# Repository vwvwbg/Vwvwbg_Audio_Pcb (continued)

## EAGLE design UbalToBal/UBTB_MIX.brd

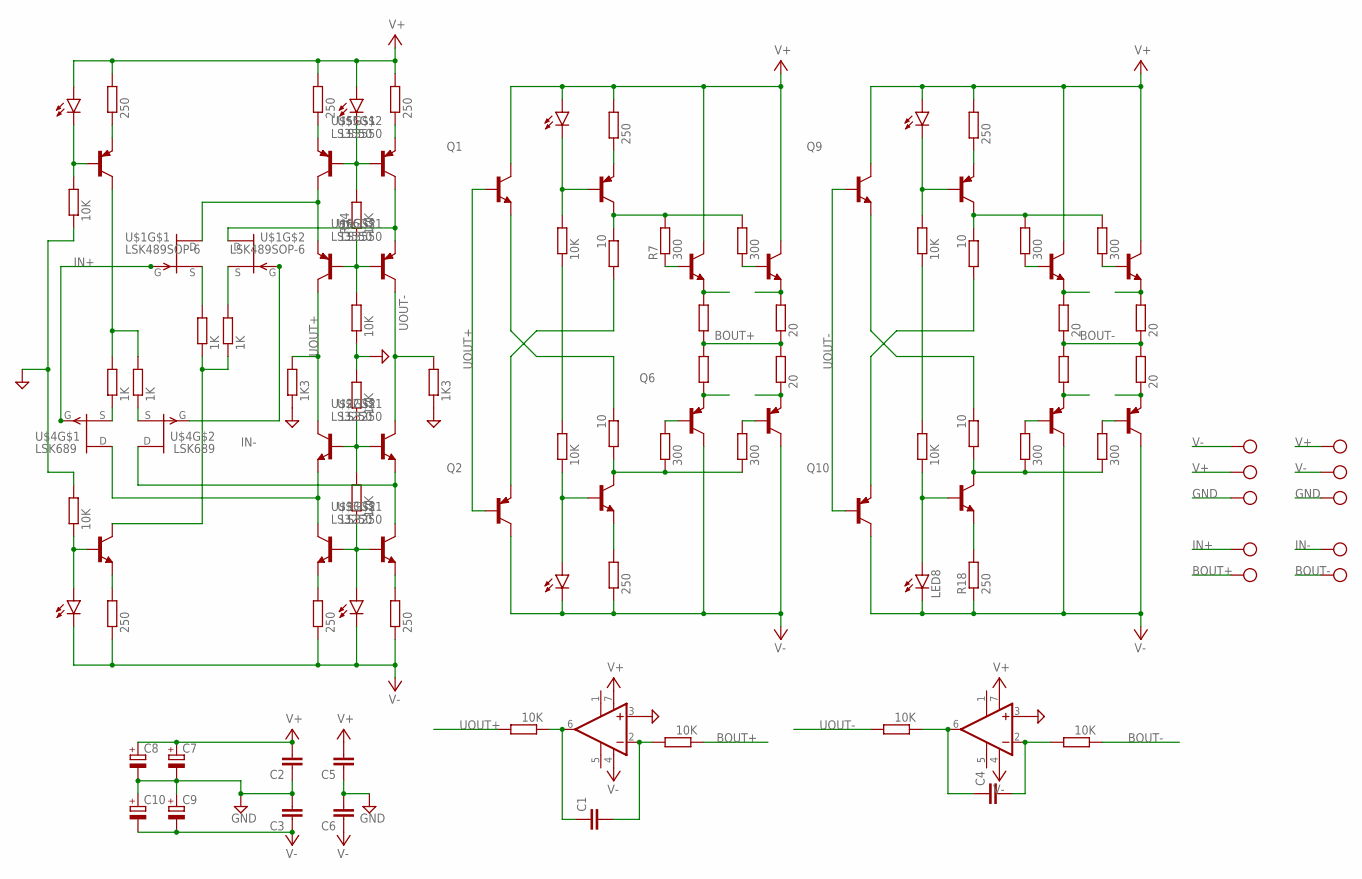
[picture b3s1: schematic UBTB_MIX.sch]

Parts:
C1, C4: C-EUC1206; C1206
C2, C3, C5, C6: C-EUC0805; C0805
C7, C8, C9, C10: CPOL-EUF; PANASONIC_F
IC1, IC2: OPA627U; SO08
LED1, LED2, LED3, LED4, LED5, LED6, LED7, LED8: LEDVWV1206; LED_SML1206
Q1, Q3, Q5, Q8, Q9, Q11, Q13, Q14, Q17: TRANSISTOR_BC846-NPN-SOT23-BEC; TRANSISTOR_SOT23-BEC
Q2, Q4, Q6, Q7, Q10, Q12, Q15, Q16, Q18: TRANSISTOR_BC856B-PNP-SOT23-BEC; TRANSISTOR_SOT23-BEC
R1, R2, R15, R18, R22, R23, R35, R36, R43, R44: 250; MINI_MELF-0204W
R3, R4, R16, R17, R19, R20, R29, R32, R33, R34, R45, R46, R48, R51: 10K; MINI_MELF-0204W
R5, R6, R21, R24: 10; MINI_MELF-0204W
R7, R8, R9, R10, R25, R26, R27, R28: 300; MINI_MELF-0204W
R11, R12, R31: R-EU_MELF0204W; MINI_MELF-0204W
R13, R14, R30, R47, R49: 20; MINI_MELF-0204W
R37, R38: 1K3; MINI_MELF-0204W
R39, R40, R41, R42: 1K; MINI_MELF-0204W
U$1: LSK489SOP-6; SOT-23-6
U$2, U$3: LS3250; SOT-23-6
U$4: LSK689; SOT-23-6
U$5, U$6: LS3550; SOT-23-6
X1, X2: CON-PHOENIX-508_MKDSN1,5/3-5,08
X3, X4: CON-PHOENIX-508_MKDSN1,5/2-5,08

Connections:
BOUT+: R11.1, R12.2, R13.1, R14.2, R17.1, X3.2
BOUT-: R30.1, R31.2, R47.1, R48.1, R49.2, X4.2
GND: C2.1, C3.2, C5.1, C6.2, C7.-, C8.-, C9.+, C10.+, IC1.3 (+IN), IC2.3 (+IN), R32.2, R33.1, R37.1, R38.1, R45.1, R46.2, X1.3, X2.3
IN+: U$1.1 (G), U$4.1 (G), X3.1
IN-: U$1.4 (G), U$4.4 (G), X4.1
unnamed: C4.1, IC2.6 (OUT), R51.1
unnamed: R35.1, U$5.2 (E)
unnamed: C4.2, IC2.2 (-IN), R48.2
unnamed: Q2.E, R5.2
unnamed: Q3.E, R2.2
unnamed: Q4.E, R1.1
unnamed: LED5.C, Q4.B, R3.2
unnamed: LED6.A, Q3.B, R4.1
unnamed: Q4.C, R5.1, R7.2, R10.2
unnamed: Q3.C, R6.2, R8.1, R9.1
unnamed: Q1.E, R6.1
unnamed: R3.1, R4.2
unnamed: Q5.B, R7.1
unnamed: Q5.E, R11.2
unnamed: Q7.B, R9.2
unnamed: Q8.B, R10.1
unnamed: Q6.B, R8.2
unnamed: Q6.E, R12.1
unnamed: C1.2, IC1.2 (-IN), R17.2
unnamed: Q8.E, R13.2
unnamed: Q7.E, R14.1
unnamed: C1.1, IC1.6 (OUT), R16.1
unnamed: R36.1, U$5.5 (E)
unnamed: Q11.E, R18.2
unnamed: Q12.E, R15.1
unnamed: LED7.C, Q12.B, R19.2
unnamed: LED8.A, Q11.B, R20.1
unnamed: Q12.C, R21.1, R25.2, R28.2
unnamed: Q11.C, R24.2, R26.1, R27.1
unnamed: Q10.E, R21.2
unnamed: Q9.E, R24.1
unnamed: R19.1, R20.2
unnamed: Q13.B, R25.1
unnamed: Q15.B, R26.2
unnamed: Q14.B, R28.1
unnamed: Q16.B, R27.2
unnamed: Q13.E, R30.2
unnamed: Q15.E, R31.1
unnamed: Q14.E, R47.2
unnamed: Q16.E, R49.1
unnamed: R22.2, U$3.5 (E)
unnamed: R23.2, U$3.2 (E)
unnamed: U$2.2 (E), U$3.4 (C), U$4.5 (D)
unnamed: U$2.5 (E), U$3.6 (C), U$4.2 (D)
unnamed: LED1.A, R29.1, U$3.1 (B), U$3.3 (B)
unnamed: R29.2, R32.1, U$2.1 (B), U$2.3 (B)
unnamed: R33.2, R34.1, U$6.1 (B), U$6.3 (B)
unnamed: U$1.2 (D), U$5.4 (C), U$6.5 (E)
unnamed: LED2.C, R34.2, U$5.1 (B), U$5.3 (B)
unnamed: U$1.5 (D), U$5.6 (C), U$6.2 (E)
unnamed: LED3.C, Q18.B, R45.2
unnamed: Q18.E, R43.1
unnamed: Q18.C, R41.2, R42.2
unnamed: R42.1, U$4.6 (S)
unnamed: R41.1, U$4.3 (S)
unnamed: R39.2, U$1.3 (S)
unnamed: R40.2, U$1.6 (S)
unnamed: Q17.C, R39.1, R40.1
unnamed: Q17.E, R44.2
unnamed: LED4.A, Q17.B, R46.1
UOUT+: Q1.B, Q2.B, R16.2, R37.2, U$2.6 (C), U$6.6 (C)
UOUT-: Q9.B, Q10.B, R38.2, R51.2, U$2.4 (C), U$6.4 (C)
V+: C2.2, C5.2, C7.+, C8.+, IC1.7 (V+), IC2.7 (V+), LED2.A, LED3.A, LED5.A, LED7.A, Q1.C, Q5.C, Q8.C, Q9.C, Q13.C, Q14.C, R1.2, R15.2, R35.2, R36.2, R43.2, X1.2, X2.1
V-: C3.1, C6.1, C9.-, C10.-, IC1.4 (V-), IC2.4 (V-), LED1.C, LED4.C, LED6.C, LED8.C, Q2.C, Q6.C, Q7.C, Q10.C, Q15.C, Q16.C, R2.1, R18.1, R22.1, R23.1, R44.1, X1.1, X2.2

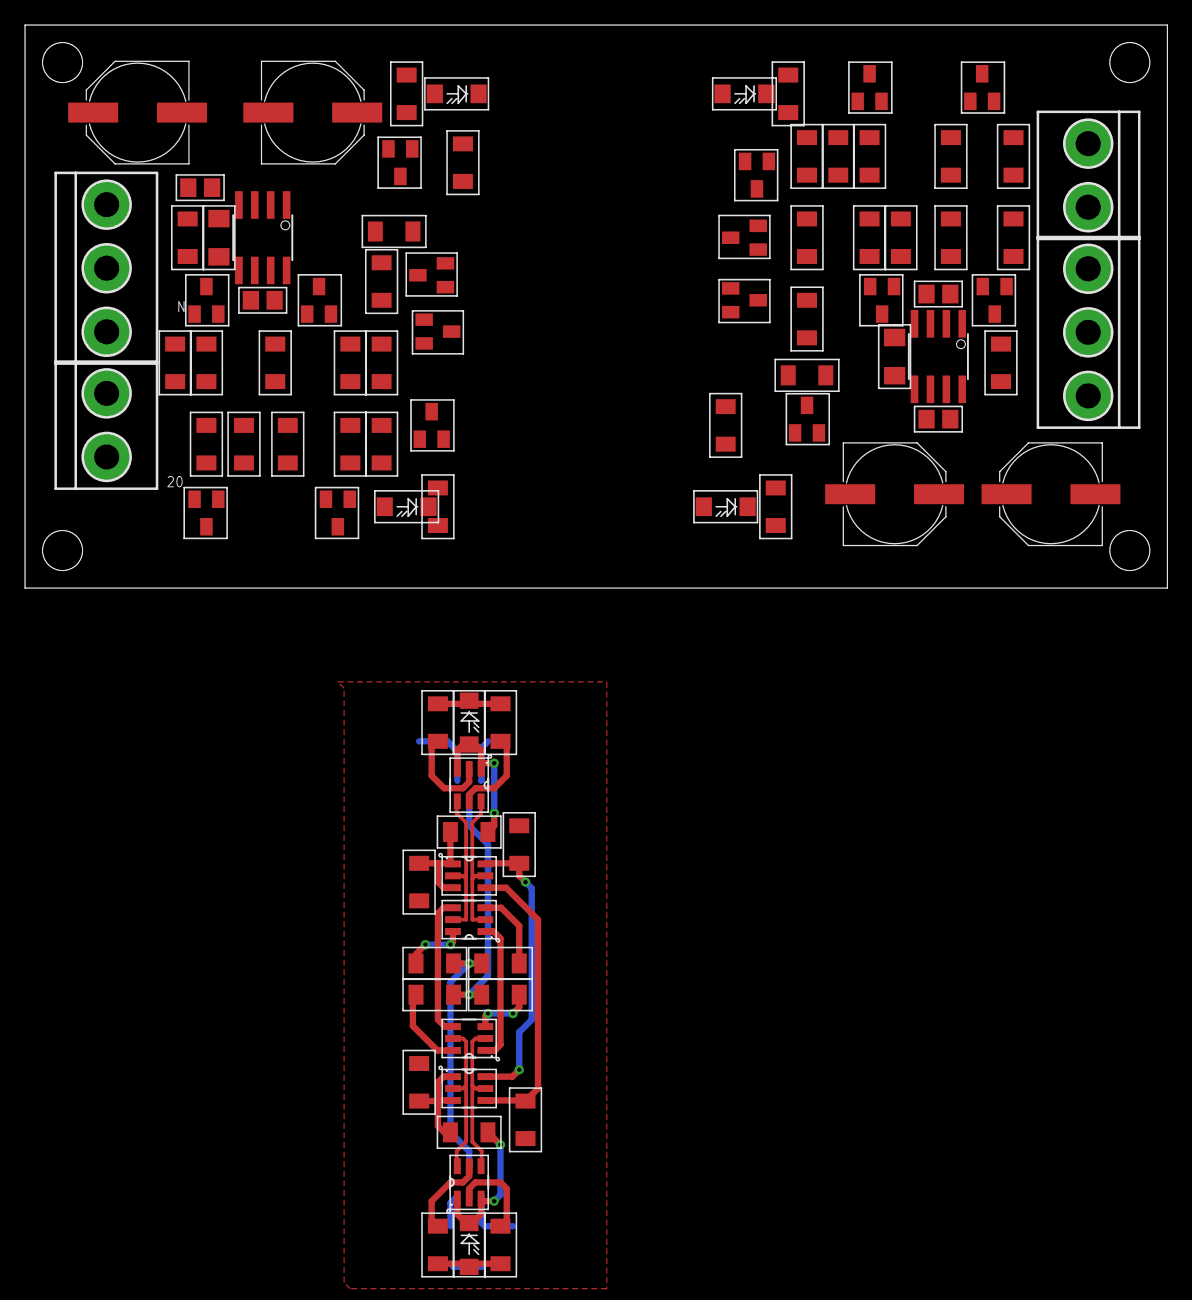
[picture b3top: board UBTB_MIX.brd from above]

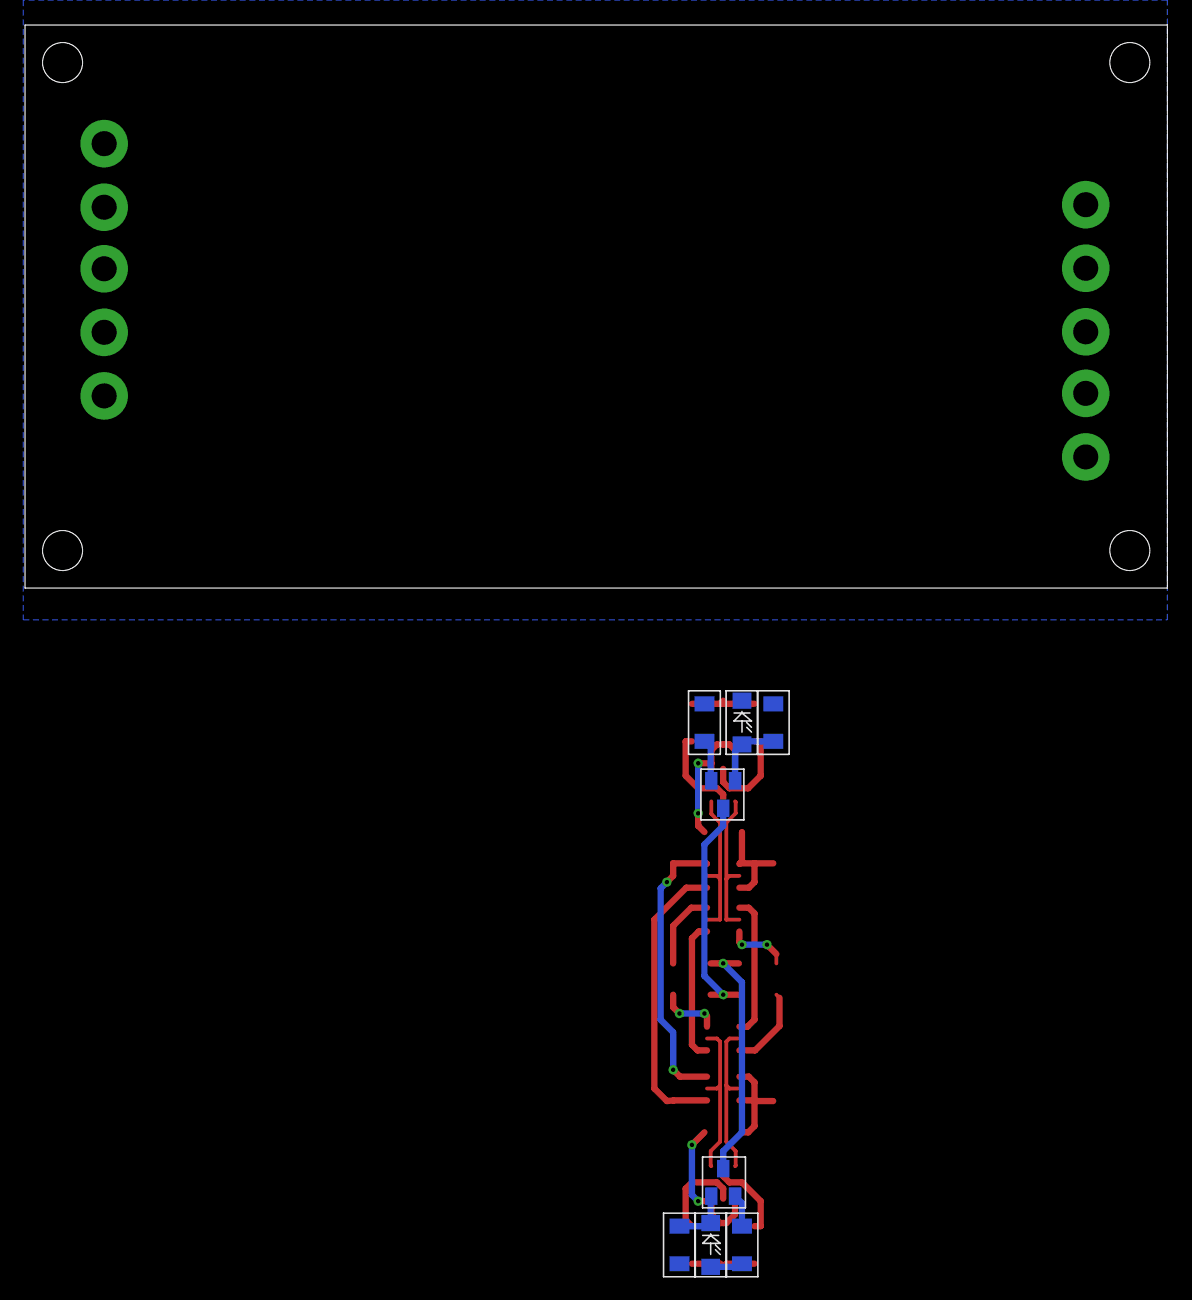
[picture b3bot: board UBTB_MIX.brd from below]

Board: 2 copper layers, 91.3 x 45.0 mm, 98 parts (8 on the bottom side), 69 nets.

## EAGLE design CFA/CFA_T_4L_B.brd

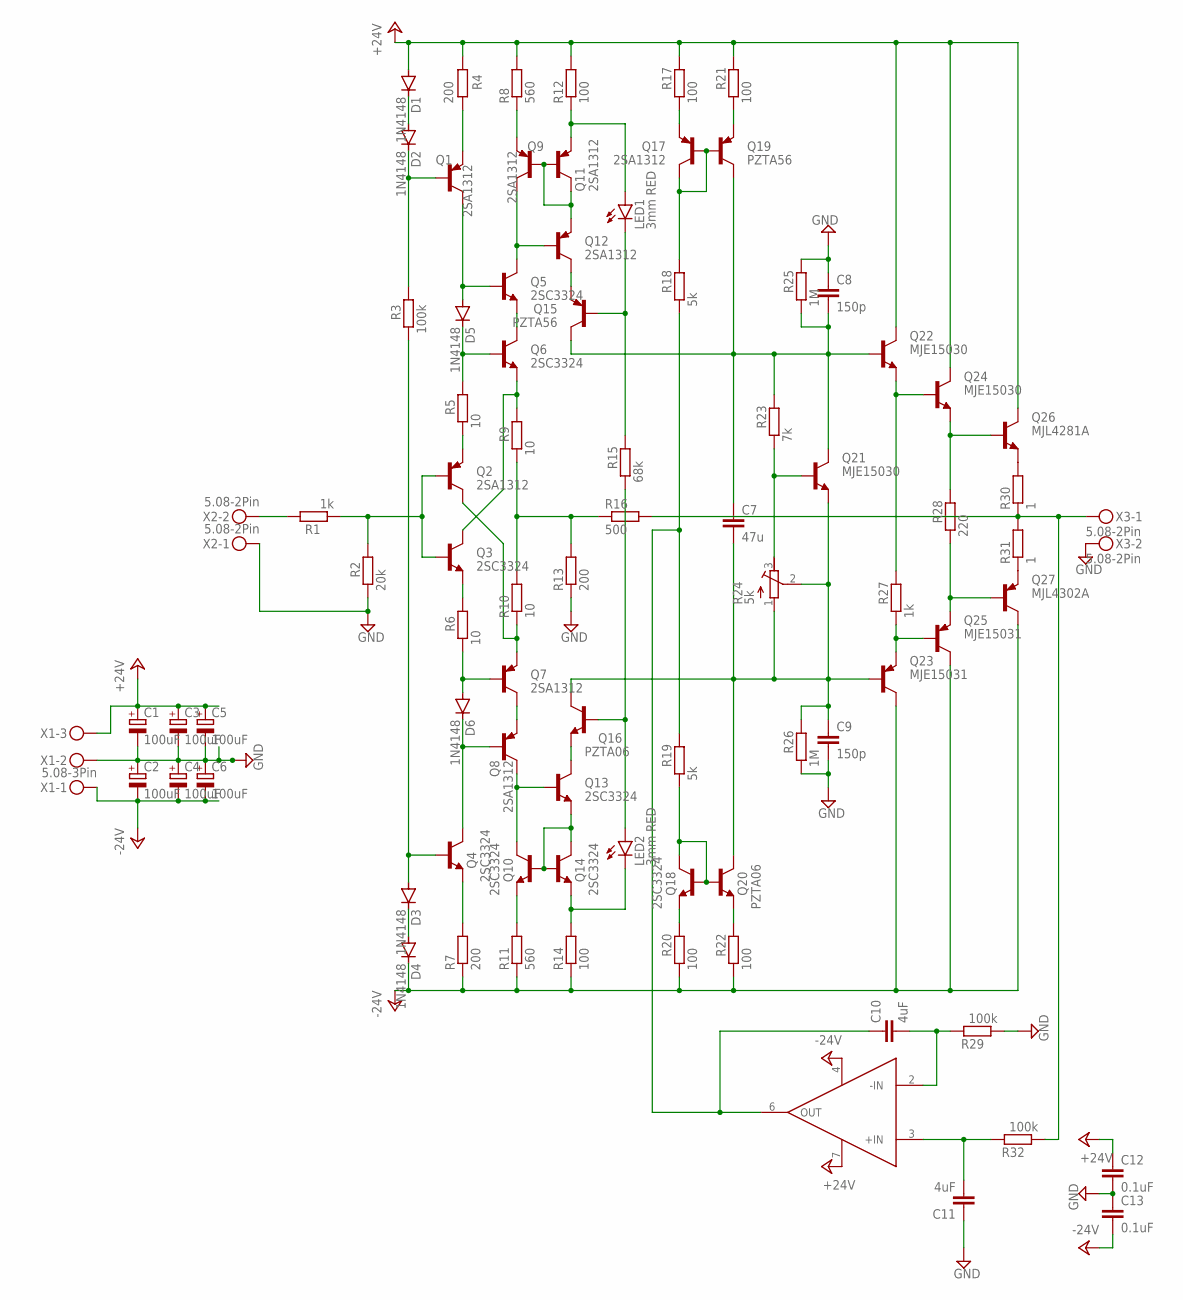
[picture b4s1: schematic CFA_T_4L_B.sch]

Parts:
C1, C2, C3, C4, C5, C6: 100uF; E3,5-8
C7: 47u; C1210
C8, C9: 150p; C0805
C10, C11: 4uF; C1210
C12, C13: 0.1uF; C0603K
D1, D2, D3, D4, D5, D6: 1N4148; SOD80C
LED1, LED2: 3mm RED; LED3MM
Q1, Q2, Q7, Q8, Q9, Q11, Q12, Q17: 2SA1312; TRANSISTOR_SOT23-BEC
Q3, Q4, Q5, Q6, Q10, Q13, Q14, Q18: 2SC3324; TRANSISTOR_SOT23-BEC
Q15, Q19: PZTA56; SOT223
Q16, Q20: PZTA06; SOT223
Q21, Q22, Q24: MJE15030; TRANSISTOR_TO220KG
Q23, Q25: MJE15031; TRANSISTOR_TO220KG
Q26: MJL4281A; TO264_TO-264
Q27: MJL4302A; TO264_TO-264
R1, R27: 1k; MINI_MELF-0204W
R2: 20k; MINI_MELF-0204W
R3, R29, R32: 100k; MINI_MELF-0204W
R4, R7, R13: 200; MINI_MELF-0204W
R5, R6, R9, R10: 10; MINI_MELF-0204W
R8, R11: 560; MINI_MELF-0204W
R12, R14, R17, R20, R21, R22: 100; MINI_MELF-0204W
R15: 68k; MINI_MELF-0204W
R16: 500; MINI_MELF-0204W
R18, R19: 5k; MINI_MELF-0204W
R23: 7k; MINI_MELF-0204W
R24: 5k; RTRIM3296W
R25, R26: 1M; MINI_MELF-0204W
R28: 220; MINI_MELF-0204W
R30, R31: 1; TO220-2
U1: OP27; DIL08
X1: 5.08-3Pin; CON-PHOENIX-508_MKDSN1,5/3-5,08
X2, X3: 5.08-2Pin; CON-PHOENIX-508_MKDSN1,5/2-5,08

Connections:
+24V: C1.+, C3.+, C5.+, C12.1, D1.A, Q22.2 (C), Q24.2 (C), Q26.C, R4.2, R8.2, R12.2, R17.2, R21.2, U1.7 (V+), X1.3
-24V: C2.-, C4.-, C6.-, C13.2, D4.C, Q23.2 (C), Q25.2 (C), Q27.C, R7.1, R11.1, R14.1, R20.1, R22.1, U1.4 (V-), X1.1
GND: C1.-, C2.+, C3.-, C4.+, C5.-, C6.+, C8.1, C9.2, C11.1, C12.2, C13.1, R2.1, R13.1, R25.2, R26.1, R29.1, X1.2, X2.1, X3.2
unnamed: C7.2, C9.1, Q16.2 (C), Q16.4 (C), Q20.2 (C), Q20.4 (C), Q21.3 (E), Q23.1 (B), R24.1 (A), R24.2 (S), R26.2
unnamed: Q21.1 (B), R23.1, R24.3 (E)
unnamed: R1.2, X2.2
unnamed: Q1.E, R4.1
unnamed: D5.A, Q1.C, Q5.B
unnamed: D1.C, D2.A
unnamed: D2.C, Q1.B, R3.2
unnamed: D5.C, Q6.B, R5.2
unnamed: Q5.E, Q6.C
unnamed: Q3.C, Q6.E, R9.2
unnamed: R9.1, R10.2, R13.2, R16.1
unnamed: Q2.C, Q7.E, R10.1
unnamed: D6.A, Q7.B, R6.1
unnamed: D6.C, Q4.C, Q8.B
unnamed: Q4.E, R7.2
unnamed: D3.C, D4.A
unnamed: Q7.C, Q8.E
unnamed: Q2.E, R5.1
unnamed: Q3.E, R6.2
unnamed: Q2.B, Q3.B, R1.1, R2.2
unnamed: Q5.C, Q9.C, Q12.B
unnamed: Q9.B, Q11.B, Q11.C, Q12.E
unnamed: Q9.E, R8.1
unnamed: LED1.A, Q11.E, R12.1
unnamed: Q12.C, Q15.3 (E)
unnamed: LED1.K (C), Q15.1 (B), R15.2
unnamed: Q10.B, Q13.E, Q14.B, Q14.C
unnamed: LED2.K (C), Q14.E, R14.2
unnamed: Q10.E, R11.2
unnamed: Q8.C, Q10.C, Q13.B
unnamed: Q13.C, Q16.3 (E)
unnamed: LED2.A, Q16.1 (B), R15.1
unnamed: C7.1, C8.2, Q15.2 (C), Q15.4 (C), Q19.2 (C), Q19.4 (C), Q21.2 (C), Q22.1 (B), R23.2, R25.1
unnamed: Q17.B, Q17.C, Q19.1 (B), R18.2
unnamed: Q18.B, Q18.C, Q20.1 (B), R19.1
unnamed: Q17.E, R17.1
unnamed: Q19.3 (E), R21.1
unnamed: R16.2, R30.1, R31.2, R32.1, X3.1
unnamed: Q18.E, R20.2
unnamed: Q20.3 (E), R22.2
unnamed: Q22.3 (E), Q24.1 (B), R27.2
unnamed: Q23.3 (E), Q25.1 (B), R27.1
unnamed: Q24.3 (E), Q26.B, R28.2
unnamed: Q25.3 (E), Q27.B, R28.1
unnamed: Q26.E, R30.2
unnamed: Q27.E, R31.1
unnamed: C10.2, R29.2, U1.2 (-IN)
unnamed: C11.2, R32.2, U1.3 (+IN)
unnamed: D3.A, Q4.B, R3.1
unnamed: C10.1, R18.1, R19.2, U1.6 (OUT)

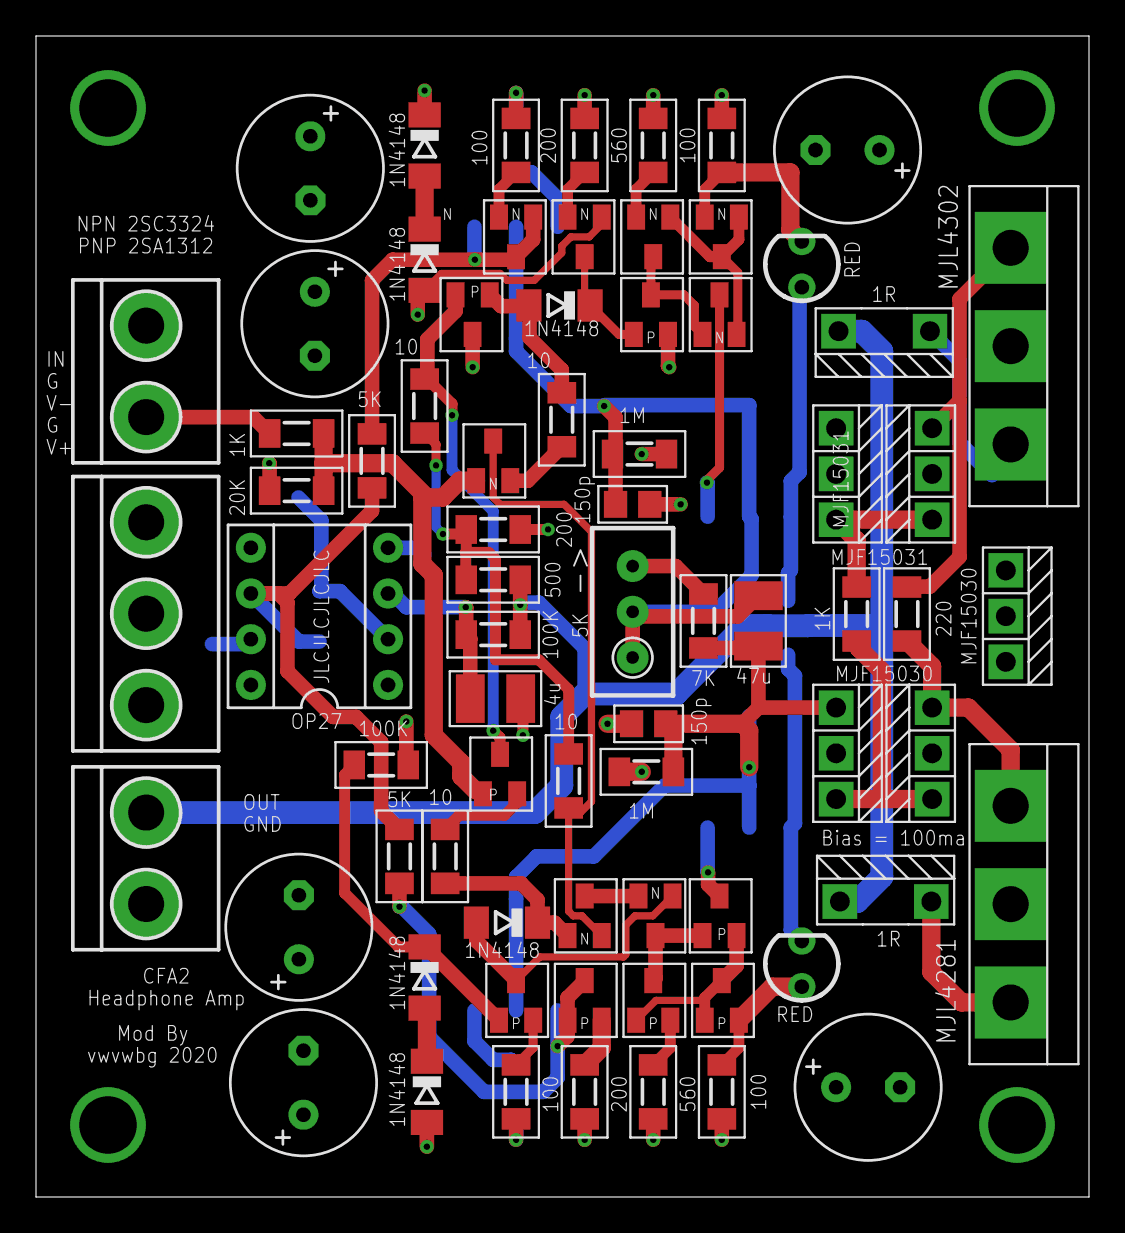
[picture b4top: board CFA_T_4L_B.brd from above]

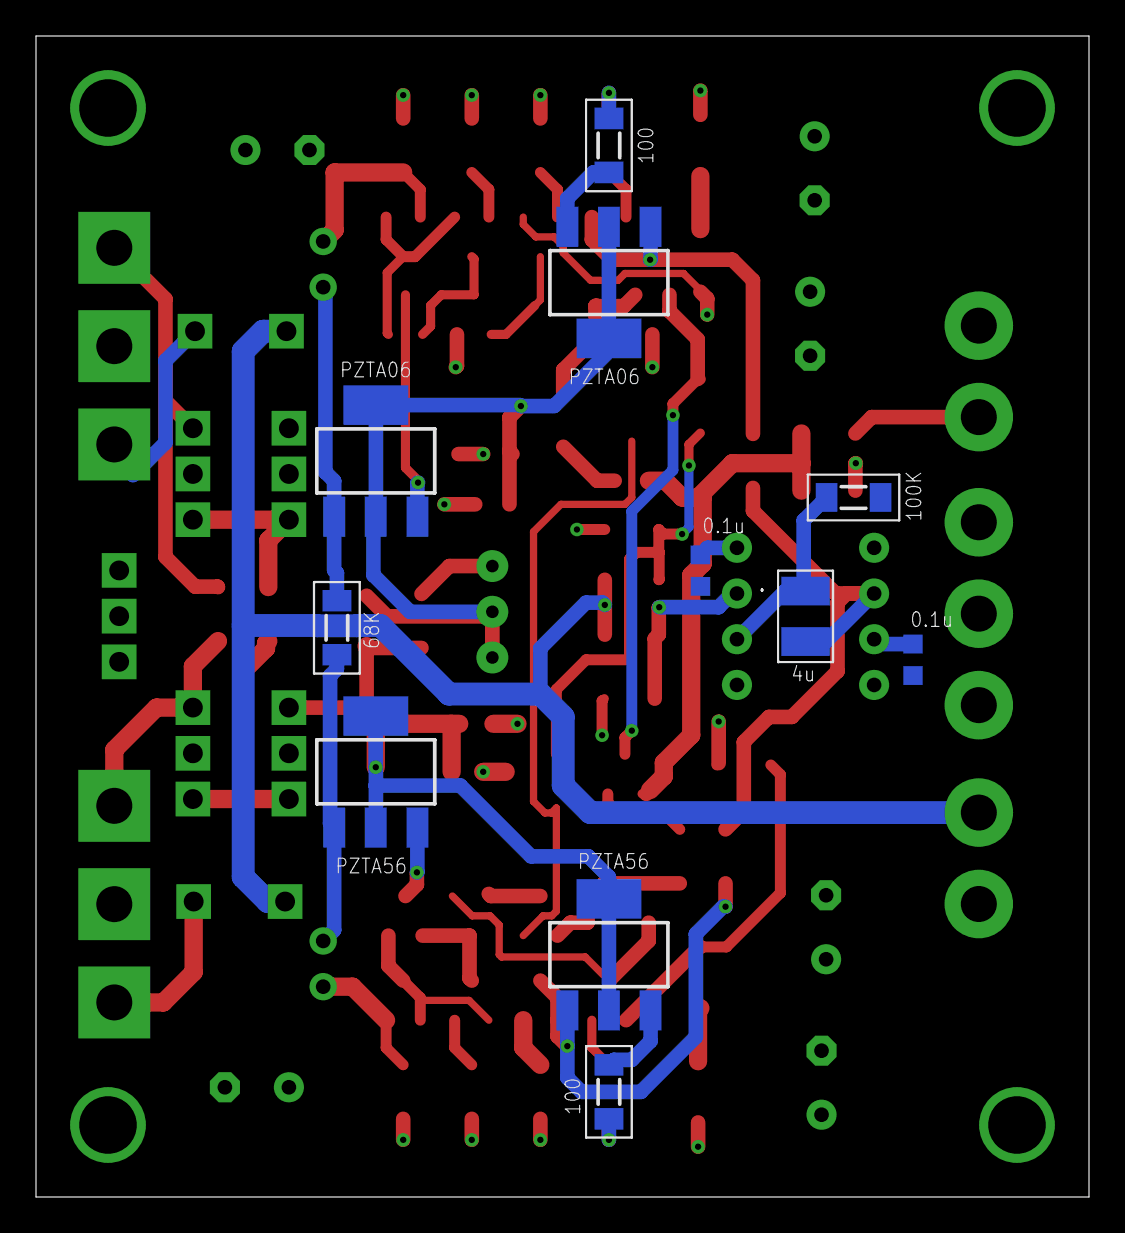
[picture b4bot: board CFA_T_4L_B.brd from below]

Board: 4 copper layers, 58.5 x 64.5 mm, 84 parts (11 on the bottom side), 53 nets.

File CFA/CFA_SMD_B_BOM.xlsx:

Qty | Value | Device | Package | Parts | MOUSER | NTD/UNIT | NTD
6 | 100uF | CPOL-EUE3.5-8 | E3,5-8 | C1, C2, C3, C4, C5, C6
2 | 4uF | C-EUC1210 | C1210 | C10, C11
2 | 0.1uF | C-EUC0603K | C0603 | C12, C13
1 | 47u | C-EUC1210 | C1210 | C7
2 | 150p | C-EUC0805 | C0805 | C8, C9
6 | 1N4148 | DIODE-SOD80C | SOD80C | D1, D2, D3, D4, D5, D6
2 | 3mm RED | LED3MM | LED3MM | LED1, LED2
8 | 2SA1312 | TRANSISTOR_BC857C-PNP-SOT23-BEC | TRANSISTOR_SOT23-BEC | Q1, Q2, Q7, Q8, Q9, Q11, Q12, Q17
2 | PZTA56 | PZTA56 | SOT223 | Q15, Q19
2 | PZTA06 | PZTA06SOT-223 | SOT223 | Q16, Q20
3 | MJE15030 | TRANSISTOR_MJE15030 | TRANSISTOR_TO220KG | Q21, Q22, Q24
2 | MJE15031 | TRANSISTOR_MJE15031 | TRANSISTOR_TO220KG | Q23, Q25
1 | MJL4281A | TO264_MJL4281 | TO264 | Q26
1 | MJL4302A | TO264_MJL4302 | TO264 | Q27
8 | 2SC3324 | TRANSISTOR_BC850-NPN-SOT23-BEC | TRANSISTOR_SOT23-BEC | Q3, Q4, Q5, Q6, Q10,Q13, Q14, Q18
2 | 1k | R-EU_MELF0204W | MINI_MELF-0204W | R1, R27
6 | 100 | R-EU_MELF0204W | MINI_MELF-0204W | R12, R14, R17, R20, R21, R22
1 | 68k | R-EU_MELF0204W | MINI_MELF-0204W | R15
1 | 500 | R-EU_MELF0204W | MINI_MELF-0204W | R16
2 | 5k | R-EU_MELF0204W | MINI_MELF-0204W | R18, R19
1 | 20k | R-EU_MELF0204W | MINI_MELF-0204W | R2
1 | 7k | R-EU_MELF0204W | MINI_MELF-0204W | R23
1 | 5k | R-TRIMM3296W | RTRIM3296W | R24
2 | 1M | R-EU_MELF0204W | MINI_MELF-0204W | R25, R26
1 | 220 | R-EU_MELF0204W | MINI_MELF-0204W | R28
3 | 100k | R-EU_MELF0204W | MINI_MELF-0204W | R3, R29, R32
2 | 1 | R-EU_TO220 | TO220-2 | R30, R31
3 | 200 | R-EU_MELF0204W | MINI_MELF-0204W | R4, R7, R13
4 | 10 | R-EU_MELF0204W | MINI_MELF-0204W | R5, R6, R9, R10
2 | 560 | R-EU_MELF0204W | MINI_MELF-0204W | R8, R11
1 | OP27 | OPA627BP | DIL08 | U1
1 | 5.08-3Pin | CON-PHOENIX-508_MKDSN1,5/3-5,08 | CON-PHOENIX-508 | X1
2 | 5.08-2Pin | CON-PHOENIX-508_MKDSN1,5/2-5,08 | CON-PHOENIX-508 | X2, X3

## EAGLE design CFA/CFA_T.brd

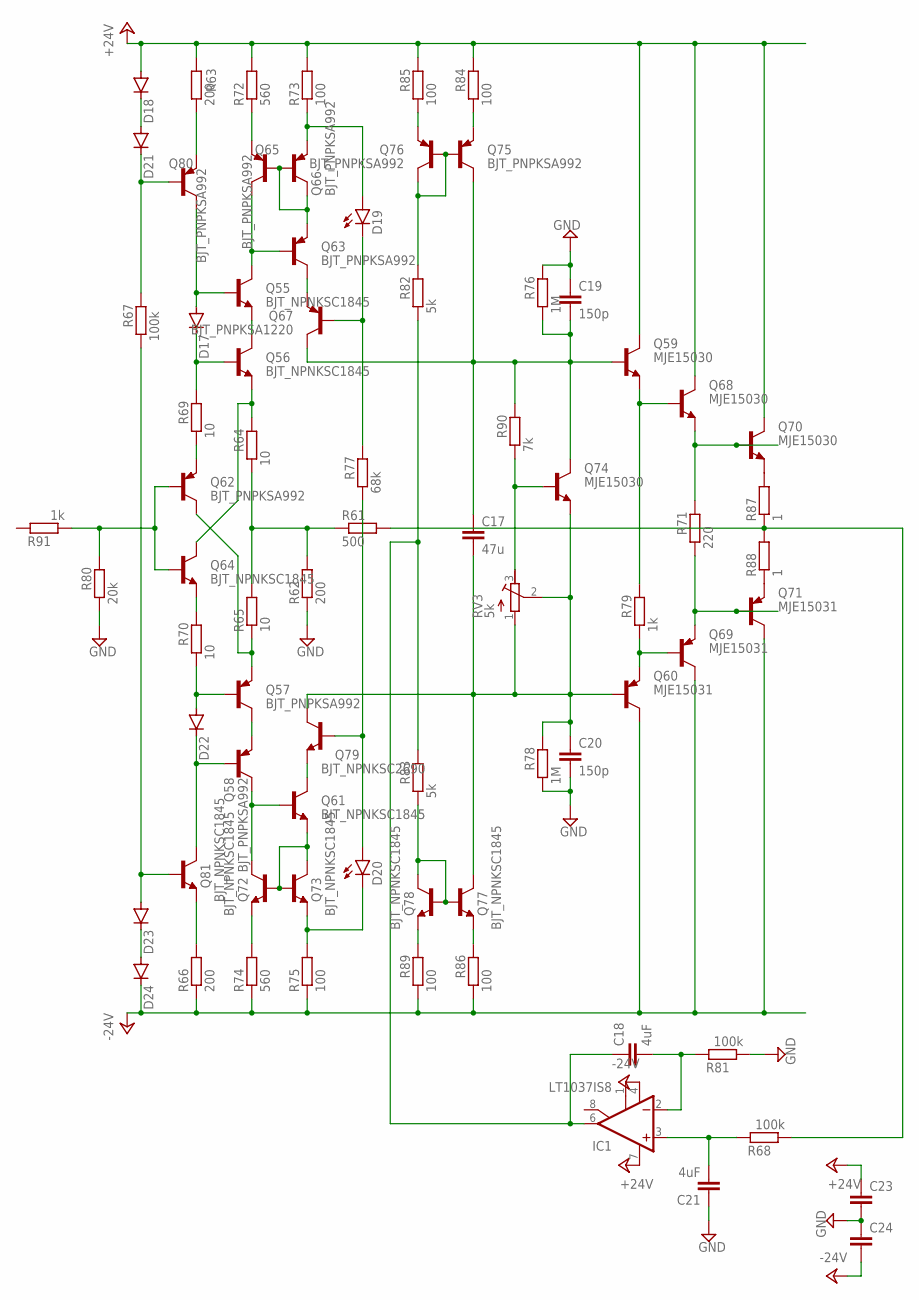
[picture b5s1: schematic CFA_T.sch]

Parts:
C17: 47u; C1210
C18, C21: 4uF; C1210
C19, C20: 150p; C0805
C23, C24: C-EUC0603K; C0603K
D17, D18, D21, D22, D23, D24: DIODE-SOD80C; SOD80C
D19, D20: LEDCHIPLED_1206; CHIPLED_1206
IC1: LT1037IS8; SOIC8
Q55, Q56, Q61, Q64, Q72, Q73, Q77, Q78, Q81: BJT_NPNKSC1845; TRANSISTOR_TO92-ECB
Q57, Q58, Q62, Q63, Q65, Q66, Q75, Q76, Q80: BJT_PNPKSA992; TRANSISTOR_TO92-ECB
Q59, Q68: MJE15030; TRANSISTOR_TO92-ECB
Q60, Q69: MJE15031; TRANSISTOR_TO92-ECB
Q67: BJT_PNPKSA1220; TRANSISTOR_TO126V
Q70: MJE15030; TO264_TO-264
Q71: MJE15031; TO264_TO-264
Q74: MJE15030; TRANSISTOR_TO220KG
Q79: BJT_NPNKSC2690; TRANSISTOR_TO126V
R61: 500; MINI_MELF-0204W
R62, R63, R66: 200; MINI_MELF-0204W
R64, R65, R69, R70: 10; MINI_MELF-0204W
R67, R68, R81: 100k; MINI_MELF-0204W
R71: 220; MINI_MELF-0204W
R72, R74: 560; MINI_MELF-0204W
R73, R75, R84, R85, R86, R89: 100; MINI_MELF-0204W
R76, R78: 1M; MINI_MELF-0204W
R77: 68k; MINI_MELF-0204W
R79, R91: 1k; MINI_MELF-0204W
R80: 20k; MINI_MELF-0204W
R82, R83: 5k; MINI_MELF-0204W
R87, R88: 1; R2512
R90: 7k; MINI_MELF-0204W
RV3: 5k; RTRIM3296W

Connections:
+24V: C23.1, D18.A, IC1.7 (V+), Q59.C, Q68.C, Q70.C, R63.2, R72.2, R73.2, R84.2, R85.2
-24V: C24.2, D24.C, IC1.4 (V-), Q60.C, Q69.C, Q71.C, R66.1, R74.1, R75.1, R86.1, R89.1
GND: C19.1, C20.2, C21.1, C23.2, C24.1, R62.1, R76.2, R78.1, R80.1, R81.1
unnamed: Q74.1 (B), R90.1, RV3.3 (E)
unnamed: Q80.E, R63.1
unnamed: D17.A, Q55.B, Q80.C
unnamed: D18.C, D21.A
unnamed: D21.C, Q80.B, R67.2
unnamed: D17.C, Q56.B, R69.2
unnamed: Q55.E, Q56.C
unnamed: Q56.E, Q64.C, R64.2
unnamed: R61.1, R62.2, R64.1, R65.2
unnamed: Q57.E, Q62.C, R65.1
unnamed: D22.A, Q57.B, R70.1
unnamed: D22.C, Q58.B, Q81.C
unnamed: Q81.E, R66.2
unnamed: D23.C, D24.A
unnamed: Q57.C, Q58.E
unnamed: Q62.E, R69.1
unnamed: Q64.E, R70.2
unnamed: Q62.B, Q64.B, R80.2, R91.1
unnamed: Q55.C, Q63.B, Q65.C
unnamed: Q63.E, Q65.B, Q66.B, Q66.C
unnamed: Q65.E, R72.1
unnamed: D19.A, Q66.E, R73.1
unnamed: Q63.C, Q67.E
unnamed: D19.C, Q67.B, R77.2
unnamed: Q61.E, Q72.B, Q73.B, Q73.C
unnamed: D20.C, Q73.E, R75.2
unnamed: Q72.E, R74.2
unnamed: Q58.C, Q61.B, Q72.C
unnamed: Q61.C, Q79.E
unnamed: D20.A, Q79.B, R77.1
unnamed: C17.1, C19.2, Q59.B, Q67.C, Q74.2 (C), Q75.C, R76.1, R90.2
unnamed: Q75.B, Q76.B, Q76.C, R82.2
unnamed: Q77.B, Q78.B, Q78.C, R83.1
unnamed: Q76.E, R85.1
unnamed: Q75.E, R84.1
unnamed: C18.1, IC1.6 (OUT), R82.1, R83.2
unnamed: R61.2, R68.1, R87.1, R88.2
unnamed: Q78.E, R89.2
unnamed: Q77.E, R86.2
unnamed: Q59.E, Q68.B, R79.2
unnamed: Q60.E, Q69.B, R79.1
unnamed: C17.2, C20.1, Q60.B, Q74.3 (E), Q77.C, Q79.C, R78.2, RV3.1 (A), RV3.2 (S)
unnamed: Q68.E, Q70.B, R71.2
unnamed: Q69.E, Q71.B, R71.1
unnamed: Q70.E, R87.2
unnamed: Q71.E, R88.1
unnamed: C18.2, IC1.2 (-IN), R81.2
unnamed: C21.2, IC1.3 (+IN), R68.2
unnamed: D23.A, Q81.B, R67.1

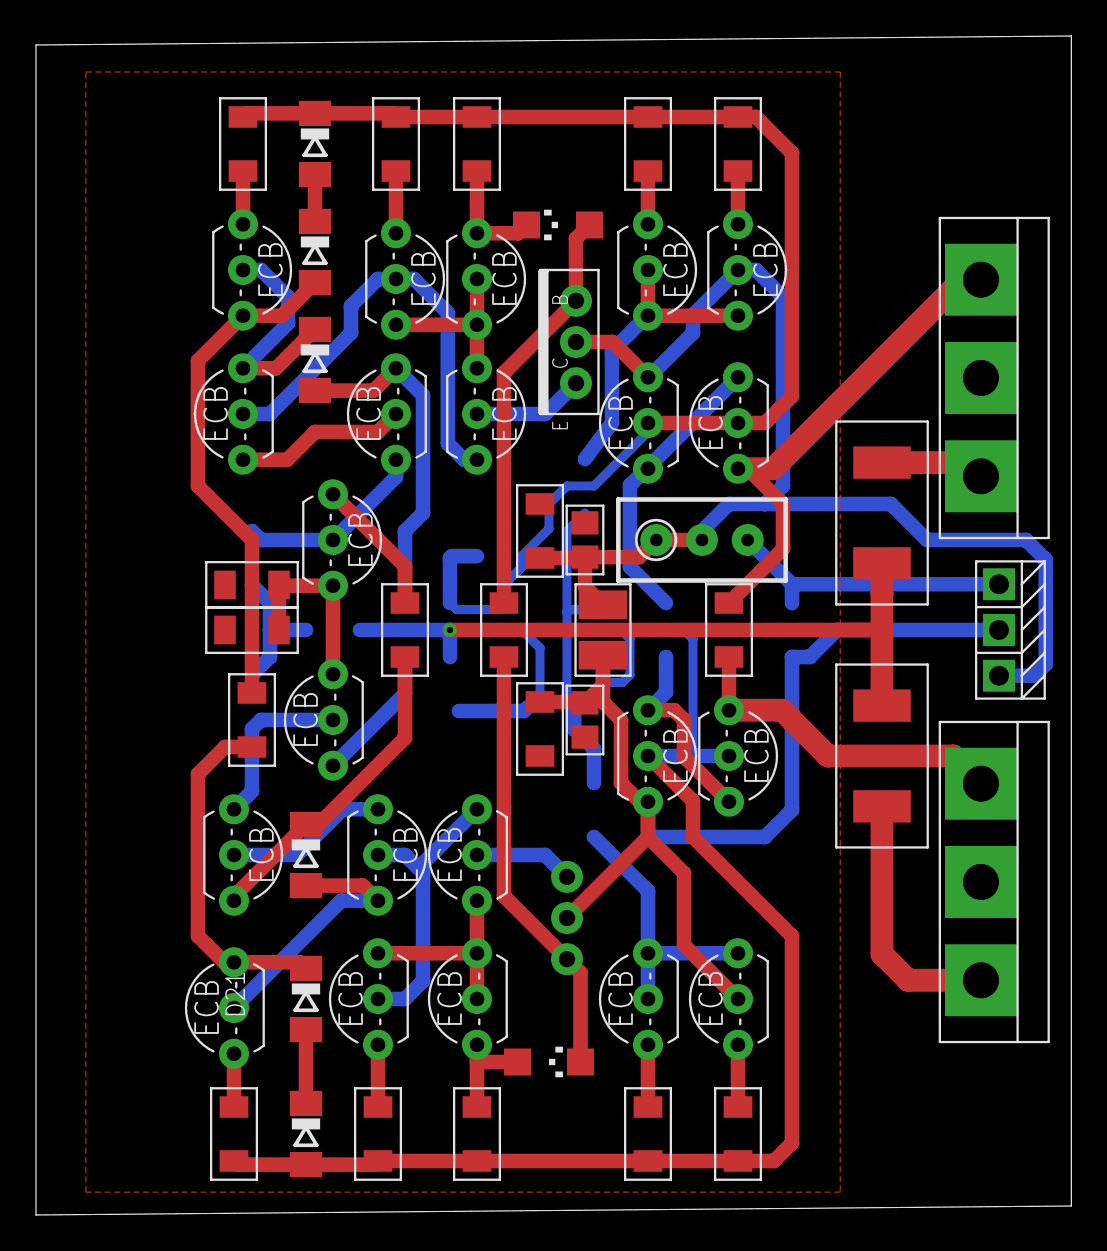
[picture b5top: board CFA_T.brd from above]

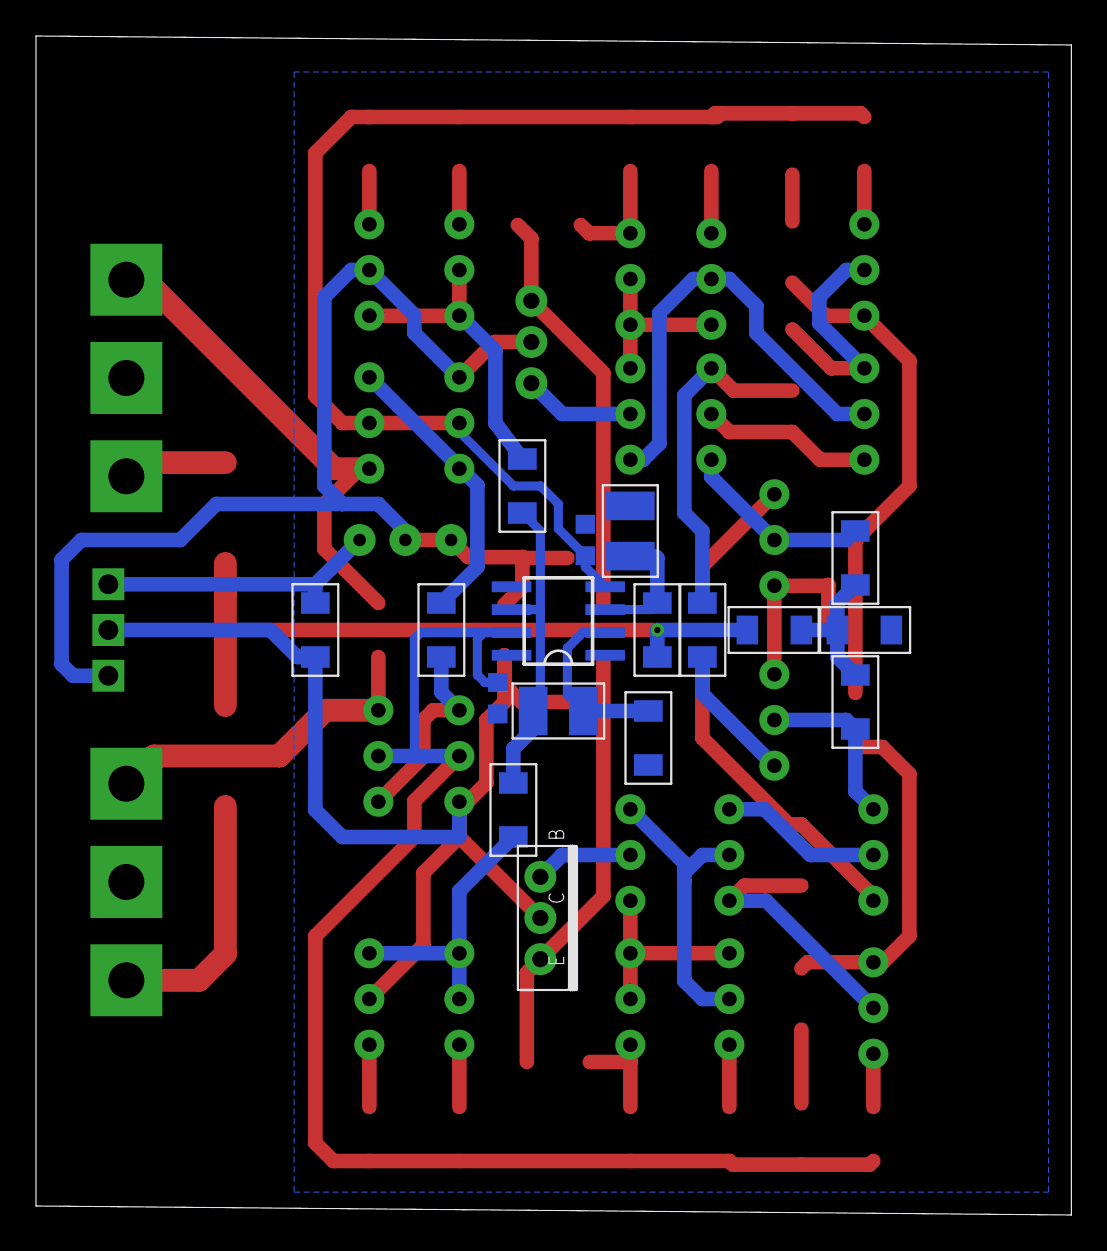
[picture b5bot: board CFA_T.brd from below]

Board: 2 copper layers, 57.5 x 65.5 mm, 75 parts (17 on the bottom side), 52 nets.

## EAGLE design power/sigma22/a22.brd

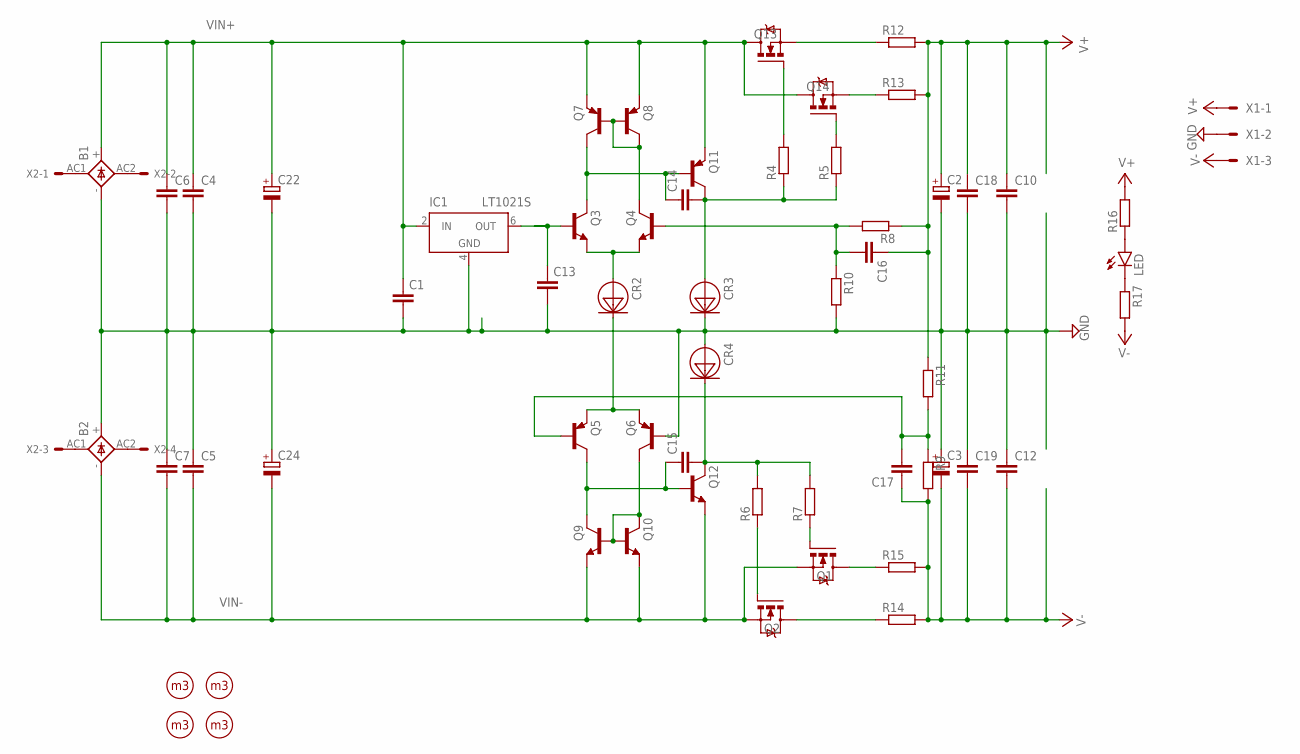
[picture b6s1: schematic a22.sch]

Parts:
B1, B2: 2KBB-R
C1, C13, C14, C15, C16, C17: C-EUC0805; C0805
C2, C3: CPOL-EUE5-13; E5-13
C4, C5, C6, C7, C10, C12, C18, C19: C-EU050-050X075; C050-050X075
C22, C24: CPOL-EUE10-25; EB25D
CR2, CR3, CR4: 1N5283; SMD
IC1: LT1021S; SOIC8
LED: LEDVWV1206; LED_SML1206
Q1, Q2, Q13, Q14: IRFZ24N; TRANSISTOR_TO220KG
Q3, Q4, Q9, Q10, Q12: BJT_NPNKSC1845; TRANSISTOR_TO92-ECB_N
Q5, Q6, Q7, Q8, Q11: BJT_PNPKSA992; TRANSISTOR_TO92-ECB_P
R4, R5, R6, R7, R8, R9, R10, R11, R16, R17: R-EU_MELF0204W; MINI_MELF-0204W
R12, R13, R14, R15: R-EU_R2512; R2512
U$1, U$2, U$3, U$4: HOLE; M3_HOLE
X1: KK-156-3
X2: KK-156-4

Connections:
GND: B1.-, B2.+, C1.2, C2.-, C3.+, C4.2, C5.1, C6.2, C7.1, C10.2, C12.1, C13.2, C18.2, C19.1, C22.-, C24.+, CR3.CATHODE, CR4.ANODE, IC1.4 (GND), Q6.B, R10.2, X1.2
unnamed: B1.AC1, X2.1
unnamed: B1.AC2, X2.2
unnamed: Q1.1 (G), R7.1
unnamed: Q13.1 (G), R4.2
unnamed: C17.2, Q5.B, R9.1, R11.2
unnamed: B2.AC1, X2.3
unnamed: B2.AC2, X2.4
unnamed: LED.A, R16.1
unnamed: CR2.CATHODE, Q5.E, Q6.E
unnamed: CR2.ANODE, Q3.E, Q4.E
unnamed: C13.1, IC1.6 (OUT), Q3.B
unnamed: Q4.C, Q7.B, Q8.B, Q8.C
unnamed: Q6.C, Q9.B, Q10.B, Q10.C
unnamed: C15.1, Q5.C, Q9.C, Q12.B
unnamed: C14.1, Q3.C, Q7.C, Q11.B
unnamed: C14.2, CR3.ANODE, Q11.C, R4.1, R5.1
unnamed: C15.2, CR4.CATHODE, Q12.C, R6.2, R7.2
unnamed: Q14.1 (G), R5.2
unnamed: LED.C, R17.1
unnamed: Q2.1 (G), R6.1
unnamed: C16.2, Q4.B, R8.2, R10.1
unnamed: Q1.2 (D), R15.1
unnamed: Q2.2 (D), R14.1
unnamed: Q13.3 (S), R12.1
unnamed: Q14.3 (S), R13.1
V+: C2.+, C10.1, C16.1, C18.1, R8.1, R11.1, R12.2, R13.2, R16.2, X1.1
V-: C3.-, C12.2, C17.1, C19.2, R9.2, R14.2, R15.2, R17.2, X1.3
VIN+: B1.+, C1.1, C4.1, C6.1, C22.+, IC1.2 (IN), Q7.E, Q8.E, Q11.E, Q13.2 (D), Q14.2 (D)
VIN-: B2.-, C5.2, C7.2, C24.-, Q1.3 (S), Q2.3 (S), Q9.E, Q10.E, Q12.E
